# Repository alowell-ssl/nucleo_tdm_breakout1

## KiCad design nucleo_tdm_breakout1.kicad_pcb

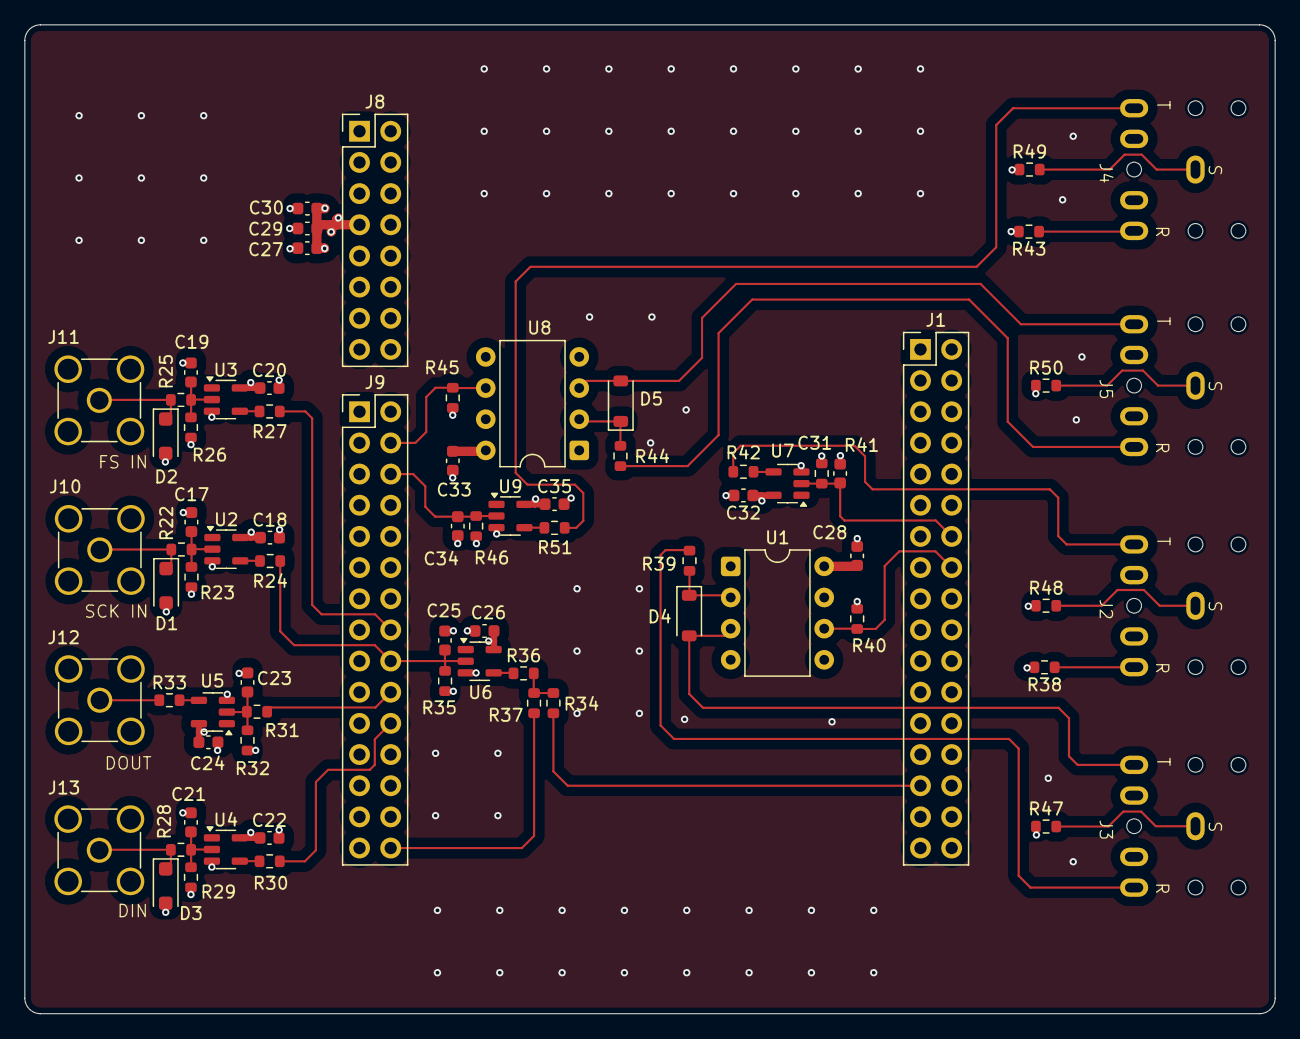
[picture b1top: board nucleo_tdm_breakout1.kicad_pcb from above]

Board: 4 copper layers, 101.9 x 80.6 mm, 74 parts (0 on the bottom side), 42 nets.

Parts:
C17, C19, C21, C23, C25, C31, C34: C_Small; C_0603_1608Metric
C18, C20, C22, C24, C26, C27, C28, C29, C30, C32, C33, C35: 100nF; C_0603_1608Metric
D1, D2, D3: D_Zener_Small; D_SOD-123F
D4, D5: 1N4148W; D_SOD-123
J1: Conn_02x17_Odd_Even; PinHeader_2x17_P2.54mm_Vertical
J2, J3, J4, J5: AudioJack3; SJ1-3523N
J8: Conn_02x08_Odd_Even; PinHeader_2x08_P2.54mm_Vertical
J9: Conn_02x15_Odd_Even; PinHeader_2x15_P2.54mm_Vertical
J10, J11, J12, J13: Conn_Coaxial; SMA_Amphenol_901-144_Vertical
R22, R25, R28, R31, R34, R37, R47, R48, R49, R50: 0; R_0603_1608Metric
R23, R26, R29, R32, R35, R41, R46: R_Small; R_0603_1608Metric
R24, R27, R30, R33, R36, R42, R51: 22; R_0603_1608Metric
R38, R43: 2.2k; R_0603_1608Metric
R39, R44: 220; R_0603_1608Metric
R40, R45: 470; R_0603_1608Metric
U1, U8: 6N137; DIP-8_W7.62mm
U2, U3, U4, U5, U6, U7, U9: 74LVC1G17; SOT-23-5

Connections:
/IO_PG1: J9.30, R37.2
/SAI1_A_FS___PE4: J9.16, R27.2
/SAI1_A_SCK___PE5: C25.1, J9.18, R24.2, R35.2, U6.2
/SAI1_A_SD___PE6: J9.20, R31.1
/SAI1_B_SD___PE3: J9.22, R30.2
/TIM2_CH1___PA0: J1.29, R34.2
/USART2_B_RX___PD6: J9.4, R45.2, U8.6 (VO)
/USART2_B_TX___PD6: C34.1, J9.6, R46.2, U9.2
/USART6_A_RX: J1.16, R40.2, U1.6 (VO)
/USART6_A_TX: C31.1, J1.14, R41.2, U7.2
/buffer/OUT: R34.1, R36.2, R37.1
/midi_out1/MIDI_OUT: J2.T, R42.2
/midi_out2/MIDI_OUT: J4.T, R51.2
GND: C17.2, C18.2, C19.2, C20.2, C21.2, C22.2, C23.2, C24.2, C25.2, C26.2, C27.2, C28.2, C29.2, C30.2, C31.2, C32.2, C33.2, C34.2, C35.2, D1.2 (A), D2.2 (A), D3.2 (A), J1.5, J1.17, J1.22, J1.27, J8.11, J8.13, J9.12, J9.23, J10.2 (Ext), J11.2 (Ext), J12.2 (Ext), J13.2 (Ext), R23.1, R26.1, R29.1, R32.1, R35.1, R41.1, R46.1, R47.1, R48.1, R49.1, R50.1, U1.5 (GND), U2.3 (GND), U3.3 (GND), U4.3 (GND), U5.3 (GND), U6.3 (GND), U7.3 (GND), U8.5 (GND), U9.3 (GND)
unnamed: C17.1, R22.2, R23.2, U2.2
unnamed: C19.1, R25.2, R26.2, U3.2
unnamed: C21.1, R28.2, R29.2, U4.2
unnamed: C23.1, R31.2, R32.2, U5.2
unnamed: D1.1 (K), J10.1 (In), R22.1
unnamed: D2.1 (K), J11.1 (In), R25.1
unnamed: D3.1 (K), J13.1 (In), R28.1
unnamed: D4.2 (A), J3.T, U1.3 (C)
unnamed: D4.1 (K), R39.1, U1.2 (A)
unnamed: D5.2 (A), J5.T, U8.3 (C)
unnamed: D5.1 (K), R44.1, U8.2 (A)
unnamed: J2.R, R38.1
unnamed: J2.S, R48.2
unnamed: J3.R, R39.2
unnamed: J3.S, R47.2
unnamed: J4.R, R43.1
unnamed: J4.S, R49.2
unnamed: J5.R, R44.2
unnamed: J5.S, R50.2
unnamed: J12.1 (In), R33.2
unnamed: R24.1, U2.4
unnamed: R27.1, U3.4
unnamed: R30.1, U4.4
unnamed: R33.1, U5.4
unnamed: R36.1, U6.4
unnamed: R42.1, U7.4
unnamed: R51.1, U9.4
VDD: C18.1, C20.1, C22.1, C24.1, C26.1, C27.1, C28.1, C29.1, C30.1, C32.1, C33.1, C35.1, J8.7, R38.2, R40.1, R43.2, R45.1, U1.8 (VCC), U2.5 (VCC), U3.5 (VCC), U4.5 (VCC), U5.5 (VCC), U6.5 (VCC), U7.5 (VCC), U8.8 (VCC), U9.5 (VCC)

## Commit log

2025-06-12 adding files
2025-06-27 adding subproject, breakout board for nucleo
